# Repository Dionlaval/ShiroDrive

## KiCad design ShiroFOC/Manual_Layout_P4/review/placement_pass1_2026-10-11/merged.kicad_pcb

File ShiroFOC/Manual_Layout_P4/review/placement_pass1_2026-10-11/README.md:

# P4 — first IC and support placement pass

11 October 2026. This pass is saved in `../../ShiroFOC_Manual.kicad_pcb`, with routing presets in the matching `.kicad_pro`. The original P4 files are backed up in `before/`. P3 and the schematics were not edited.

## Result

All 18 ICs are within the 45 × 45 mm board outline. Forty existing footprints have changed position or orientation, and the schematic's fitted R618 has been added. The MCU and centred, locked encoder retain their original positions. The outline, mounting holes, power wire pads and six-layer stack are preserved.

There are now 212 footprint origins on the board, up from 179. Sixty-six remain staged: 50 fitted/default parts, 15 DNP parts and the SWD programming footprint. Fifty of these staged footprints belong to the DC-link capacitor bank (44 fitted, six DNP); the remaining input capacitors, bleeder and interfaces still need space. This pass therefore completes the IC placement, not the entire component placement.

[Front/back placement preview](preview/final/overview.png) shows actual footprint geometry and references. Both views use top-view coordinates; the back view is not mirrored. Copper fills are omitted for clarity. J1/J101 are intentionally shown as wire pads without the unused connector plastics.

## Placement decisions

- Preserve the repeated three-phase arrangement at the right, MCU below centre, auxiliary supplies above, and interfaces along the left and lower edges.
- Place U701 and its decoupling/I²C support between the MCU and auxiliary section, with access to the MCU's upper pins. Clear the centred encoder by moving the interfering resistors.
- Keep U602/U603 at the lower side, improve U602's position and nearby support, and bring C603/C605 close to their ICs. Add R618, 49.9 kΩ, between U604 ILIM and GND, matching its existing schematic symbol and path.
- Put C3/C7/C11 on the back alongside their phase stages, with VM pads facing the bridge's plated VM connections. Place TH701/TH702/TH703 beside their respective stages. Place C101/C102/C103/C110 as the first local DC-link ceramic bank.
- Bring reset, brake-input and temperature-divider support onto the board near the MCU/quiet analogue area. Leave the reset switch with the remaining interface placement rather than force it into the phase region.
- Rotate C203 to correct the existing bootstrap pad-to-track mismatch. Rotate R503 to shorten the brake-driver output/gate connection and add short local auxiliary/driver connections.

These are placement choices intended to support short loops and accessible routing. Final loop areas and return paths still depend on completing the copper.

## Routing setup and copper changes

Standard selectable trace widths are 0.1524 mm and 0.254 mm (6 and 10 mil). Default/analogue classes use 6 mil; gate and logic-power classes use 10 mil. Standalone through vias use 0.5 mm pads with 0.3 mm drills. Embedded plated thermal pads in the power footprints retain their native geometry.

The existing power-width and USB differential-pair settings are retained; their final sizing needs the power routing and final impedance stack. Existing preliminary traces were not globally resized.

Eighteen obsolete or obstructing copper guide objects were removed, and 32 short local track/via objects were added. Remaining half-bridge traces continue to indicate routing intent. See the individual manifests and `integration_repairs.json` for the exact changes.

## Verification

Native KiCad 9 DRC used the project rules and freshly filled zones. The comparison baseline was also refilled with the project settings.

The structural check passed: all existing electrical pad identities and schematic paths are preserved, R618 matches the schematic, and the MCU/encoder, board outline, four mounting holes and rule-area keepouts are unchanged. Four unused unnumbered mechanical locating pads belonging to J1/J101 were removed for the wire-only arrangement; their electrical pads are unchanged. All 18 IC envelopes fit; U1/U2/U3 have no courtyard polygons, so their native body/pad bounds were checked instead. Details are in `validation/final_structural_validation.json`.

| Native result | Before | After |
| --- | ---: | ---: |
| Errors | 64 | 33 |
| Warnings | 331 | 401 |
| Unconnected items | 456 | 444 |

No new error pairs were introduced, comparing violation type and item UUIDs. The remaining errors are 22 clearances, nine copper-to-edge clearances, and the two intentional connector-plastic courtyard overlaps at J1/J101. The latter are not physical conflicts for the planned soldered wires. New warnings are unfinished silkscreen and dangling ends left by guide removal; they have not been suppressed. See `final/drc.json` and `drc_comparison.json`.

Confidence: geometry, identities, dimensions and DRC results are verified from the native files. Routing quality remains a provisional placement assessment; this is not a completed routing or manufacturing release.

## Next layout pass

1. Finish the remaining DC-link bank/protection and service-interface placement, including reset/SWD and external temperature connections. Resolve the space required by the staged bulk capacitors before locking the power region. Optional DNP snubbers remain staged.
2. Route each phase's switching and gate/source-return loops, then the Kelvin shunt pairs; replace the preliminary copper as needed. Keep temperature and other quiet analogue traces clear of the switching nodes.
3. Finish MCU, sensor, feedback-selection and interface connections, with local decoupling returns and ground stitching.
4. Resolve the remaining real clearance/edge findings, finish silkscreen, refill zones, and run full connectivity/DRC checks again.

The primary board and project files are the working deliverables. Candidate files under `aux/`, `digital/`, `power/`, `control/` and `final/` are review history, not alternative project versions to edit.

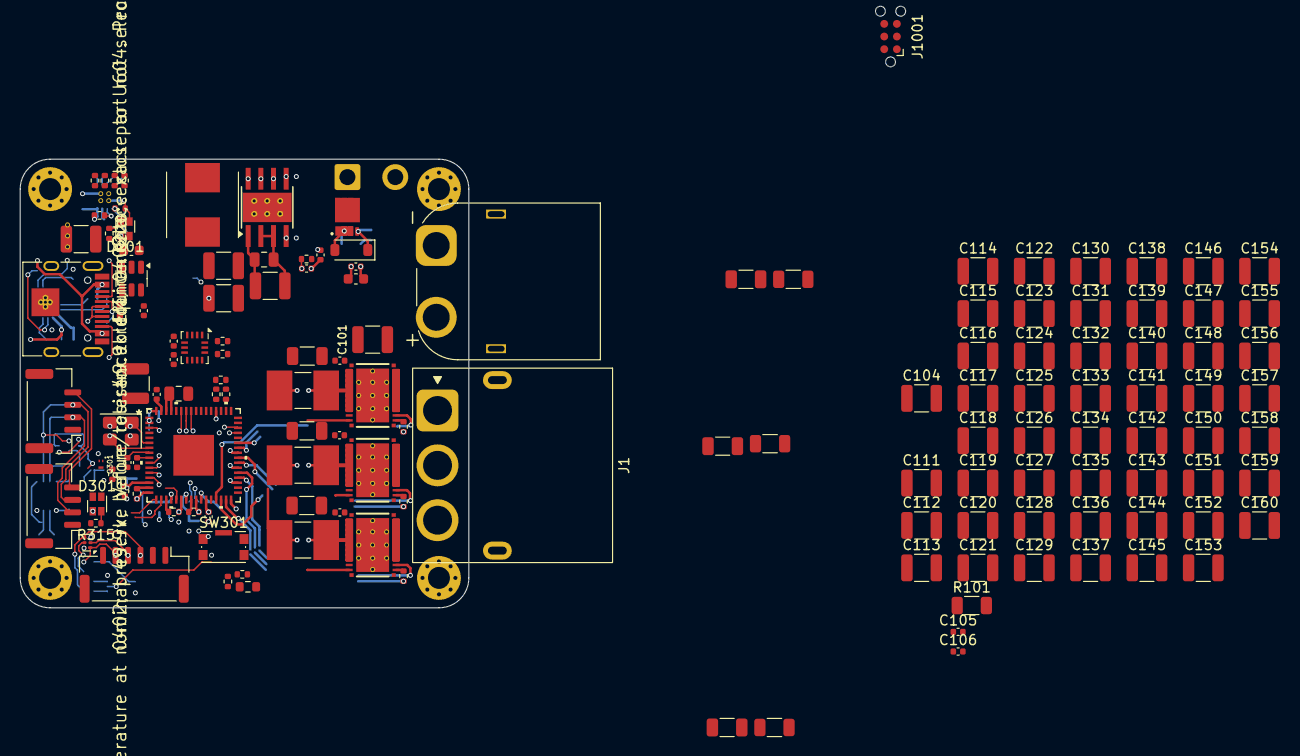
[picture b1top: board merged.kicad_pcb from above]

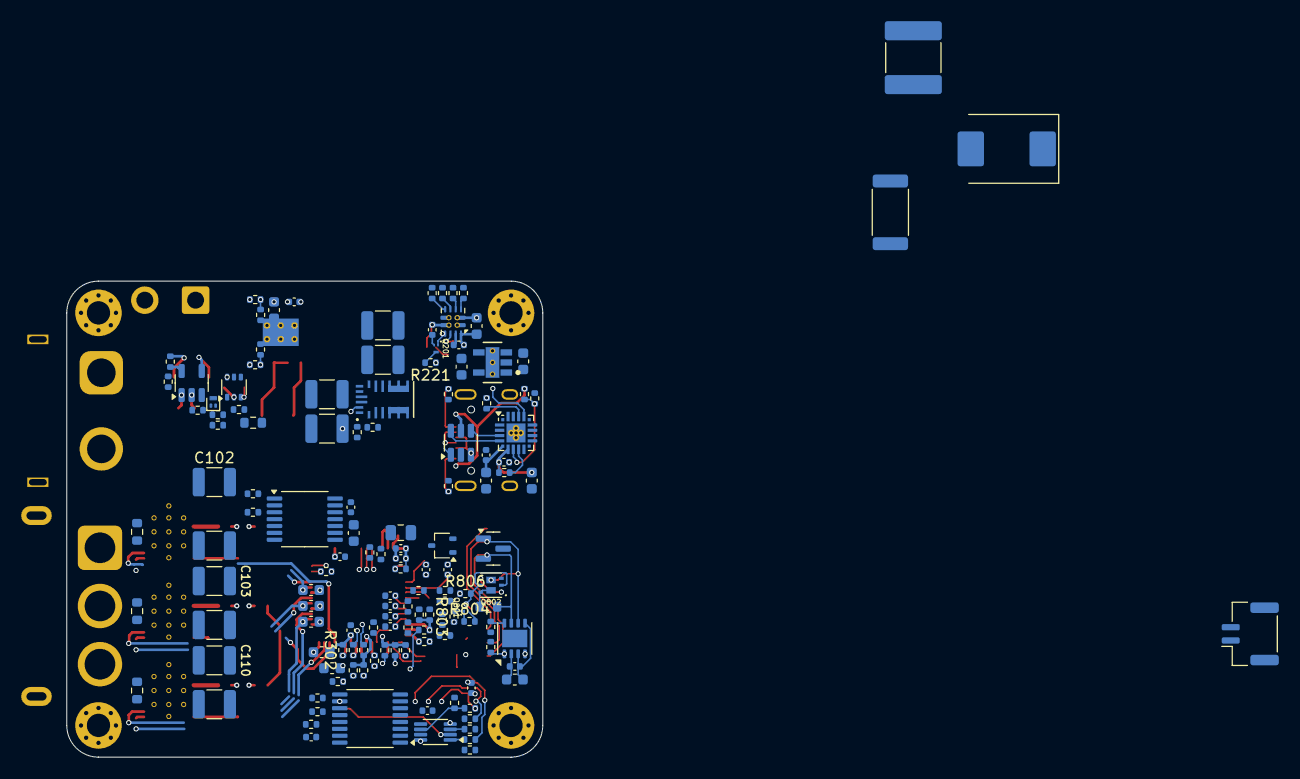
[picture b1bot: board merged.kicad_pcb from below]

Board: 6 copper layers, 45.0 x 45.0 mm, 278 parts (135 on the bottom side), 149 nets.

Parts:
C1, C5, C9, C108, C314, C711, C712, C713: 10nF; C_0402_1005Metric
C2, C6, C10: 1uF; C_1206_3216Metric
C3, C7, C11: 4.7uF; C_1210_3225Metric
C4, C8, C12: 220nF; C_0603_1608Metric
C101, C102, C103, C110, C111, C112, C113, C114, C115, C116, C117, C118, C119, C120, C121, C122, C123, C124, C127, C128, C129, C130, C131, C132, C133, C134, C135, C136, C137, C138, C139, C140, C141, C144, C145, C146, C147, C148, C149, C150, C151, C152, C153, C154, C155, C156, C157, C158: 10uF; C_1210_3225Metric
C104: 4.7uF 100V X7R; C_1210_3225Metric
C105: 100nF 100V X7R; C_0402_1005Metric
C106: 10nF 100V C0G; C_0402_1005Metric
C107: RC DAMP C - TUNE; C_2220_5750Metric
C125, C126, C142, C143, C159, C160: 10uF DNP; C_1210_3225Metric
C201: 2.2uF 100V X7R; C_1210_3225Metric
C202: 220nF 100V X7R; C_0805_2012Metric
C203, C209, C211, C301, C303, C305, C307, C310, C601, C603, C605, C701, C702, C801, C902, C904: 100nF; C_0402_1005Metric
C204, C304, C306, C602, C802: 1uF; C_0603_1608Metric
C205, C206, C214, C215: 22uF 25V X7R; C_1210_3225Metric
C208: 1uF 10V; C_0603_1608Metric
C210: 22uF 10V X7R; C_1210_3225Metric
C212, C213: 2.2uF 10V X7R; C_0603_1608Metric
C218, C219: 22uF 16V X7R; C_1210_3225Metric
C302: 10uF 10V; C_0805_2012Metric
C308, C309: 10pF C0G; C_0402_1005Metric
C311: 220nF 100V; C_0805_2012Metric
C312: 10uF 25V X7R; C_1210_3225Metric
C313: 100nF 25V; C_0402_1005Metric
C413, C423, C433: TUNE DNP; C_1206_3216Metric
C501: 1uF 25V; C_0603_1608Metric
C502, C503, C604: 100nF 50V; C_0402_1005Metric
C504: 1nF C0G; C_0402_1005Metric
C505: 100nF 16V; C_0402_1005Metric
C606: 4.7uF 16V X7R; C_0603_1608Metric
C607: 100nF 16V X7R; C_0402_1005Metric
C901, C903: 4.7uF 10V; C_0603_1608Metric
D101: VM TVS - SELECT AFTER TEST; D_SMC
D201, D301: LTST-C19HE1WT; LED_LiteOn_LTST-C19HE1WT
D501: BZT52C12 12V; D_SOD-123
D502: BAT54CM; SOT-883
D505: BAT54SW; SOT-323_SC-70
D601: TPD3E001DRYR; TPD3E001_DRY6
D801: PESD2CANFD24V-T; SOT-23
H1, H2, H3, H4: M2 PTH; MountingHole_2.2mm_M2_Pad_Via
J1: MR60PW-M; AMASS_MR60PW-M_1x03_P5.50mm_Horizontal
J101: AMASS XT60PW-M; AMASS_XT60PW-M_1x02_P7.20mm_Horizontal
J201: USB-C service; USB_C_Receptacle_HRO_TYPE-C-31-M-12
J501: BRAKE RESISTOR; SolderWire-0.75sqmm_1x02_P4.8mm_D1.25mm_OD2.3mm
J502: BRAKE NTC; JST_GH_SM02B-GHS-TB_1x02-1MP_P1.25mm_Horizontal
J601: EXT ENCODER / HALL; JST_GH_BM06B-GHS-TBT_1x06-1MP_P1.25mm_Vertical
J801: CAN 1; JST_GH_BM04B-GHS-TBT_1x04-1MP_P1.25mm_Vertical
J802: CAN 2; JST_GH_BM04B-GHS-TBT_1x04-1MP_P1.25mm_Vertical
J1001: TC2030-NL SWD; Tag-Connect_TC2030-IDC-NL_2x03_P1.27mm_Vertical
L201: 47uH / 1.9A; WE_LHMI_7050_74437349470
Q201, Q301, Q801: CSD17483F4; CSD17483F4_YJC0003A
Q501: ISZ080N10NM6 100V; ISZ080N10NM6_TSDSON8_FL
Q802: CSD87502Q2; CSD87502Q2_DLV0006A
R1, R3, R5: 0.5m 1%; R_Shunt_LR2512D_0m5_3W_Kelvin
R2, R4, R6: 4R7; R_0402_1005Metric
R101: 470k 0.25W; R_1206_3216Metric
R102: RC DAMP R - TUNE; R_2512_6332Metric
R103: 560k 0.1% 75V; R_0603_1608Metric
R105, R419, R429, R439: 28k 0.1%; R_0402_1005Metric
R106, R312, R711, R712, R713, R901: 1k; R_0402_1005Metric
R201: 100k 1%; R_0402_1005Metric
R202: 11.1k 1%; R_0402_1005Metric
R203, R204: 5.1k; R_0402_1005Metric
R206: 15.0k 1%; R_0402_1005Metric
R207, R209, R211, R213: 5.10k 1%; R_0402_1005Metric
R208: 10.0k 1%; R_0402_1005Metric
R210, R212: 22.0k 1%; R_0402_1005Metric
R214: 80.6k 1%; R_0402_1005Metric
R215, R220, R305, R306, R307, R309, R311, R315, R501, R504, R505, R604, R801, R805, R806: 10k; R_0402_1005Metric
R216: 34.0k 0.1%; R_0402_1005Metric
R217: 6.49k 0.1%; R_0402_1005Metric
R218, R219, R310, R615, R616, R617, R804: 100k; R_0402_1005Metric
R221: 33k; R_0402_1005Metric
R301, R302: 0R; R_0402_1005Metric
R303: 2k2; R_0402_1005Metric
R304: 15k; R_0402_1005Metric
R308, R715: 2.2k; R_0402_1005Metric
R313, R314: 22R; R_0402_1005Metric
R410, R420, R430, R441, R442, R443: 56k 0.1%; R_0402_1005Metric
R415, R425, R435: TUNE DNP; R_1206_3216Metric
R417, R418, R427, R428, R437, R438: 1k 0.1%; R_0402_1005Metric
R502, R611: 33R; R_0402_1005Metric
R503: 4.7R; R_0402_1005Metric
R506: 470k 1% 75V; R_0603_1608Metric
R509: 13.3k 1%; R_0402_1005Metric
R510: 1M 1%; R_0402_1005Metric
R511: 10k 1%; R_0402_1005Metric
R512, R701, R702, R703: 4.7k 1%; R_0402_1005Metric
R605, R606, R607, R902, R903: 100R; R_0402_1005Metric
R618: 49.9k 1%; R_0402_1005Metric
R802: 120R 1%; R_0603_1608Metric
R803: 4.7k; R_0402_1005Metric
R904: 22.1k 1%; R_0402_1005Metric
R905: 47.5k 1%; R_0402_1005Metric
SW301: RESET; SW_Push_1P1T-SH_NO_CK_KMR2xxG
TH701, TH702, TH703: 10k NTC B3380; R_0603_1608Metric
U1, U2, U3: CSD88599Q5DC; DMM0022A
U4: STSPIN32G4; QFN_IN32G4_STM
U201: LMR36510FADDAR; LMR36510_DDA
U202: USBLC6-2SC6; USBLC6_SOT23_6
U203: TPS2121RUXR; TPS2121_RUX
U204: TLV75533PDYDR; TLV75533_DYD_GND
U205: MPM3620AGQV-Z; IC18_MPM3620AGQV-Z_MNP
U501: UCC27517ADBVR; UCC27517A_DBV5
U502: TLV3012BIDCKR; SOT-363_SC-70-6
U601: AS5047P-ATSM; AS5047P_TSSOP14
U602: TMUX1574PW; TMUX1574_PW16
U603: 74LVC3G17; VSSOP-8_2.3x2mm_P0.5mm
U604: TPS2553DBVR; SOT-23-6
U701: BMI323; BMI323_LGA14
U801: TCAN3413DRBR; TCAN3413_DRB8
U901: CP2102N-A02-GQFN20; SiliconLabs_QFN-20-1EP_3x3mm_P0.5mm_EP1.8x1.8mm_ThermalVias
Y301: 24MHz 7pF; Crystal_SMD_3225-4Pin_3.2x2.5mm

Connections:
3V3: C213.1, C301.1, C302.1, C307.1, C503.1, C601.1, C602.1, C603.1, C605.1, C701.1, C702.1, C801.1, C802.1, C901.1, C902.1, C903.1, C904.1, D505.2 (K), J1001.1 (VCC), R301.1, R303.1, R305.1, R308.1, R309.1, R310.1, R511.1, R604.1, R701.1, R702.1, R703.1, R715.1, R801.1, R805.1, R901.1, U4.1 (REG3V3/VDD), U4.2 (VBAT), U4.64 (REGIN), U204.5 (OUT), U502.6 (VDD), U601.11 (VDD), U601.12 (VDD3V3), U602.16 (VDD), U603.8 (VCC), U701.5 (VDDIO), U701.8 (VDD), U701.12 (CSB), U801.3 (VCC), U801.5 (VIO), U901.6 (VDD), U901.7 (VREGIN)
5V_BAT: C218.1, C219.1, R206.1, R210.1, R216.1, U203.7 (IN1), U205.7 (OUT), U205.8 (OUT), U205.9 (OUT)
5V_SYS: C210.1, C211.1, C212.1, C606.1, D201.4 (A), D301.4 (A), R215.1, U203.1 (OUT), U203.8 (OUT), U204.1 (IN), U204.3 (EN), U604.1 (IN), U604.3 (EN)
5V_USB: C208.1, J201.A4 (VBUS), J201.A9 (VBUS), J201.B4 (VBUS), J201.B9 (VBUS), R208.1, R212.1, R904.1, U202.5 (VBUS), U203.2 (IN2)
/5 V / 3.3 V power/10V_FB: R201.2, R202.1, U201.5 (FB)
/5 V / 3.3 V power/10V_GOOD: R218.2, R219.1, U201.4 (PG), U205.17 (EN)
/5 V / 3.3 V power/U205_AGND: R217.2, U205.3 (AGND)
/5 V / 3.3 V power/U205_SW: U205.4 (SW), U205.5 (SW), U205.6 (SW)
/Brake chopper/BRAKE_NTC_RAW: J502.1, R511.2, R512.1
/Brake chopper/BRAKE_OV_CMD: D502.2 (A2), R510.1, U502.1 (OUT)
/Brake chopper/BRAKE_PWM_DRV: D502.3 (CC), R505.1, U501.3 (IN+)
/CAN interface/CANH_BUS: D801.2 (CANH_IN), J801.2, J802.2, R802.1, U801.7 (CANH)
/CAN interface/CANL_BUS: D801.1 (CANL_IN), J801.3, J802.3, Q802.3 (D2), U801.6 (CANL)
/CAN interface/CAN_SHIELD: J801.4, J802.4
/Current / temperature/NTC_A_RAW: R701.2, R711.1, TH701.1
/Current / temperature/NTC_B_RAW: R702.2, R712.1, TH702.1
/Current / temperature/NTC_C_RAW: R703.2, R713.1, TH703.1
/Current / temperature/OPN_U1: R418.2, R419.2, U4.16 (-)
/Current / temperature/OPN_V1: R428.2, R429.2, U4.22 (-)
/Current / temperature/OPN_W1: R438.2, R439.2, U4.25 (-)
/Current / temperature/OPP_U1: R410.2, R417.2, R441.1, U4.14 (+)
/Current / temperature/OPP_V1: R420.2, R427.2, R442.1, U4.20 (+)
/Current / temperature/OPP_W1: R430.2, R437.2, R443.1, U4.23 (+)
/External feedback/EXT_VCC: C607.1, J601.1, U604.6 (OUT)
/External feedback/FB_ESD_RAIL: C604.1, D601.6 (VCC)
/MCU / clock / SWD/NRST: C310.1, J1001.3 (~RESET), R303.2, SW301.1, U4.8 (PG10/NRST)
/MCU / clock / SWD/SWCLK: J1001.4 (SWCLK), U4.50 (PA14/SWCLK)
/MCU / clock / SWD/SWDIO: J1001.2 (SWDIO), U4.49 (PA13/SWDIO)
/Three-phase bridge/LS_SOURCE_U: C413.2, R3.1 (POWER+), U1.12 (PGND), U1.13 (PGND), U1.14 (PGND), U1.15 (PGND), U1.16 (PGND), U1.17 (PGND), U1.18 (PGND), U1.19 (PGND), U1.20 (PGND)
/Three-phase bridge/LS_SOURCE_V: C423.2, R1.1 (POWER+), U2.12 (PGND), U2.13 (PGND), U2.14 (PGND), U2.15 (PGND), U2.16 (PGND), U2.17 (PGND), U2.18 (PGND), U2.19 (PGND), U2.20 (PGND)
/Three-phase bridge/LS_SOURCE_W: C433.2, R5.1 (POWER+), U3.12 (PGND), U3.13 (PGND), U3.14 (PGND), U3.15 (PGND), U3.16 (PGND), U3.17 (PGND), U3.18 (PGND), U3.19 (PGND), U3.20 (PGND)
/USB service/CP2102_RST_N: R901.2, U901.9 (RST)
/USB service/CP2102_VBUS_SENSE: R904.2, R905.1, U901.8 (VBUS)
/USB service/UART_BRIDGE_RX: R903.2, U901.17 (RXD)
/USB service/UART_BRIDGE_TX: R902.1, U901.18 (TXD)
/USB service/USB_CC1: J201.A5 (CC1), R203.1
/USB service/USB_CC2: J201.B5 (CC2), R204.1
/USB service/USB_DM: U202.6 (IO1), U901.5 (D-)
/USB service/USB_DM_CONN: J201.A7 (D-), J201.B7 (D-), U202.1 (IO1)
/USB service/USB_DP: U202.4 (IO2), U901.4 (D+)
/USB service/USB_DP_CONN: J201.A6 (D+), J201.B6 (D+), U202.3 (IO2)
AS5047P_CS_N: R309.2, U4.51 (PA15), U601.1 (CSn)
BOOTSTRAP1: C4.2, U4.41 (BOOTSTRAP1)
BOOTSTRAP2: C8.2, U4.38 (BOOTSTRAP2)
BOOTSTRAP3: C12.2, U4.35 (BOOTSTRAP3)
BRAKE_PWM: R501.1, R502.1, U4.60 (PB9)
CAN_STB: R801.2, U4.28 (PB10), U801.8 (STB)
CAN_TERM_DISABLE: R803.1, U4.5 (PC15)
CAN_TERM_GATE: Q301.1 (G), Q801.3 (D), Q802.2 (G1), Q802.5 (G2), R806.2
EXT_FEEDBACK_SELECT: R306.1, U4.53 (PD2), U602.1 (SEL)
EXT_SENSOR_FAULT_N: R604.2, U4.3 (PC13), U604.4 (~FAULT)
FDCAN1_RX: U4.47 (PA11), U801.4 (RXD)
FDCAN1_TX: R805.2, U4.48 (PA12), U801.1 (TXD)
FEEDBACK_A_H1: U4.57 (PB6), U602.4 (D1)
FEEDBACK_B_H2: U4.58 (PB7), U602.7 (D2)
FEEDBACK_I_H3: R307.1, U4.59 (PB8/BOOT0), U602.9 (D3)
GHS1: R2.2, U4.43 (GHS1)
GHS2: R4.2, U4.40 (GHS2)
GHS3: R6.2, U4.37 (GHS3)
GLS1: U1.22 (GL), U4.29 (GLS1)
GLS2: U2.22 (GL), U4.30 (GLS2)
GLS3: U3.22 (GL), U4.31 (GLS3)
GND: C1.2, C2.2, C3.2, C5.2, C6.2, C7.2, C9.2, C10.2, C11.2, C101.2, C102.2, C103.2, C104.2, C105.2, C106.2, C107.2, C108.2, C110.2, C111.2, C112.2, C113.2, C114.2, C115.2, C116.2, C117.2, C118.2, C119.2, C120.2, C121.2, C122.2, C123.2, C124.2, C125.2, C126.2, C127.2, C128.2, C129.2, C130.2, C131.2, C132.2, C133.2, C134.2, C135.2, C136.2, C137.2, C138.2, C139.2, C140.2, C141.2, C142.2, C143.2, C144.2, C145.2, C146.2, C147.2, C148.2, C149.2, C150.2, C151.2, C152.2, C153.2, C154.2, C155.2, C156.2, C157.2, C158.2, C159.2, C160.2, C201.2, C202.2, C204.2, C205.2, C206.2, C208.2, C209.2, C210.2, C211.2, C212.2, C213.2, C214.2, C215.2, C218.2, C219.2, C301.2, C302.2, C303.2, C304.2, C305.2, C306.2, C307.2, C308.2, C309.2, C310.2, C311.2, C312.2, C313.2, C314.2, C501.2, C502.2, C503.2, C504.2, C505.2, C601.2, C602.2, C603.2, C604.2, C605.2, C606.2, C607.2, C701.2, C702.2, C711.2, C712.2, C713.2, C801.2, C802.2, C901.2, C902.2, C903.2, C904.2, D101.2 (A), D501.2 (A), D505.1 (A), D601.3 (GND), D801.3 (GND), J101.1, J201.A1 (GND), J201.A12 (GND), J201.B1 (GND), J201.B12 (GND), J201.S1 (SHIELD), J502.2, J502.MP (MOUNT), J601.2, J601.6, J601.MP (MOUNT), J801.1, J801.MP (MOUNT), J802.1, J802.MP (MOUNT), J1001.5 (GND), Q201.2 (S), Q301.2 (S), Q501.1 (S), Q501.2 (S), Q501.3 (S), Q801.2 (S), R1.4 (POWER-), R3.4 (POWER-), R5.4 (POWER-), R101.2, R105.2, R202.2, R203.2, R204.2, R207.2, R209.2, R211.2, R213.2, R214.2, R219.2, R220.2, R306.2, R307.2, R311.2, R315.2, R441.2, R442.2, R443.2, R501.2, R504.2, R505.2, R509.2, R615.2, R616.2, R617.2, R618.2, R804.2, R905.2, SW301.2, SW301.SH (B), TH701.2, TH702.2, TH703.2, U4.32 (PGND), U4.65 (VSS/EP), U201.1 (PGND), U201.9 (GND), U202.2 (GND), U203.12 (GND), U204.2 (GND), U205.12 (PGND), U205.13 (PGND), U205.14 (PGND), U501.2 (GND), U501.4 (IN-), U502.2 (GND), U601.5 (TEST), U601.13 (GND), U602.2 (S1A), U602.5 (S2A), U602.8 (GND), U602.11 (S3A), U603.4 (GND), U604.2 (GND), U701.1 (SDO/SA0), U701.6 (GNDIO), U701.7 (GND), U801.2 (GND), U801.9 (EP), U901.3 (GND), U901.12 (GND), U901.21 (EP), Y301.2, Y301.4
HS_RETURN_U: C4.1, U1.2 (SH), U4.42 (OUT1)
HS_RETURN_V: C8.1, U2.2 (SH), U4.39 (OUT2)
HS_RETURN_W: C12.1, U3.2 (SH), U4.36 (OUT3)
I2C2_SCL: R308.2, U4.21 (PC4), U701.13 (SCK/SCL)
I2C2_SDA: R715.2, U4.44 (PA8), U701.14 (SDI/SDA)
IMU_INT1: U4.17 (PA4), U701.4 (INT1)
IMU_INT2: U4.18 (PA5), U701.9 (INT2)
INPUT_MUX_ENABLE_N: R305.2, U4.4 (PC14), U602.15 (EN_N)
NTC_BRAKE: C505.1, D505.3 (COM), R512.2, U4.10 (PC1)
NTC_PHASE_A: C711.1, R711.2, U4.12 (PC3)
NTC_PHASE_B: C712.1, R712.2, U4.11 (PC2)
NTC_PHASE_C: C713.1, R713.2, U4.13 (PA0)
unnamed: C107.1, R102.2
unnamed: C413.1, R415.2
unnamed: C423.1, R425.2
unnamed: C433.1, R435.2
unnamed: D201.3 (BK), R220.1
unnamed: D201.2 (GK), R221.1
unnamed: D301.3 (BK), R315.1
unnamed: D301.1 (RK), R304.2
unnamed: D501.1 (K), Q501.4 (G), R503.2, R504.1
unnamed: D502.1 (A1), R502.2
unnamed: D601.1 (IO1), J601.5, R607.1
unnamed: D601.2 (IO2), D601.5 (NC), J601.4, R606.1
unnamed: D601.4 (IO3), J601.3, R605.1
unnamed: J501.1, Q501.5 (D), Q501.6 (D), Q501.7 (D), Q501.8 (D)
unnamed: Q201.3 (D), R221.2
unnamed: Q301.3 (D), R304.1
unnamed: Q801.1 (G), R803.2, R804.1
unnamed: Q802.6 (D1), R802.2
unnamed: Q802.1 (S1), Q802.4 (S2)
unnamed: R103.2, R105.1, R106.1
unnamed: R310.2, R311.1, R312.1
unnamed: R605.2, R615.1, U603.1
unnamed: R606.2, R616.1, U603.3
unnamed: R607.2, R617.1, U603.6
unnamed: R2.1, U1.1 (GH)
unnamed: R4.1, U2.1 (GH)
unnamed: R6.1, U3.1 (GH)
unnamed: C308.1, U4.6 (PF0), Y301.1
unnamed: C309.1, U4.7 (PF1), Y301.3
unnamed: C314.1, R312.2, U4.52 (SCREF)
unnamed: C203.1, U201.7 (BOOT)
unnamed: C203.2, L201.1, U201.8 (SW)
unnamed: C204.1, U201.6 (VCC)
unnamed: R208.2, R209.1, U203.3 (CP2)
unnamed: R214.1, U203.10 (ILM)
unnamed: R210.2, R211.1, U203.5 (OV1)
unnamed: R212.2, R213.1, U203.4 (OV2)
unnamed: R206.2, R207.1, U203.6 (PR1)
unnamed: C209.1, U203.11 (SS)
unnamed: R216.2, R217.1, U205.1 (FB)
unnamed: R503.1, U501.5 (OUT)
unnamed: C504.1, R506.2, R509.1, R510.2, U502.3 (IN+)
unnamed: U502.4 (IN-), U502.5 (REF)
unnamed: R313.2, U601.2 (CLK)
unnamed: R611.1, U601.3 (MISO)
unnamed: R314.2, U601.4 (MOSI)
unnamed: U602.3 (S1B), U603.7
unnamed: U602.6 (S2B), U603.5
unnamed: U602.10 (S3B), U603.2
unnamed: R618.1, U604.5 (ILIM)
OPO_U1: R419.1, U4.15 (OUT)
OPO_V1: R429.1, U4.19 (OUT)
OPO_W1: R439.1, U4.24 (OUT)
PHASE_U: J1.1 (U), R415.1, U1.3 (VSW), U1.4 (VSW), U1.5 (VSW), U1.6 (VSW), U1.7 (VSW), U1.8 (VSW), U1.9 (VSW), U1.10 (VSW), U1.11 (VSW)
PHASE_V: J1.2 (V), R425.1, U2.3 (VSW), U2.4 (VSW), U2.5 (VSW), U2.6 (VSW), U2.7 (VSW), U2.8 (VSW), U2.9 (VSW), U2.10 (VSW), U2.11 (VSW)
PHASE_W: J1.3 (W), R435.1, U3.3 (VSW), U3.4 (VSW), U3.5 (VSW), U3.6 (VSW), U3.7 (VSW), U3.8 (VSW), U3.9 (VSW), U3.10 (VSW), U3.11 (VSW)
PWR_SOURCE_STATUS: Q201.1 (G), R215.2, U203.9 (ST)
SHUNT_U_SENSE_N: R3.3 (SENSE-), R418.1
SHUNT_U_SENSE_P: R3.2 (SENSE+), R417.1
SHUNT_V_SENSE_N: R1.3 (SENSE-), R428.1
SHUNT_V_SENSE_P: R1.2 (SENSE+), R427.1
SHUNT_W_SENSE_N: R5.3 (SENSE-), R438.1
SHUNT_W_SENSE_P: R5.2 (SENSE+), R437.1
SPI3_MISO: R611.2, U4.55 (PB4)
SPI3_MOSI_MCU: R314.1, U4.56 (PB5)
SPI3_SCK_MCU: R313.1, U4.54 (PB3)
USB_UART_RX: R902.2, U4.46 (PA10)
USB_UART_TX: R903.1, U4.45 (PA9)
VBUS_MUX_IN: R106.2, U602.13 (S4A), U602.14 (S4B)
VBUS_SENSE: C108.1, U4.9 (PC0), U602.12 (D4)
VCC: C205.1, C206.1, C214.1, C215.1, C312.1, C313.1, C501.1, C502.1, L201.2, R201.1, R218.1, R806.1, U4.63 (VCC), U205.16 (IN), U501.1 (VDD)
VDDA: C303.1, C304.1, R301.2, R302.1, U4.27 (VDDA)
VM: C1.1, C2.1, C3.1, C5.1, C6.1, C7.1, C9.1, C10.1, C11.1, C101.1, C102.1, C103.1, C104.1, C105.1, C106.1, C110.1, C111.1, C112.1, C113.1, C114.1, C115.1, C116.1, C117.1, C118.1, C119.1, C120.1, C121.1, C122.1, C123.1, C124.1, C125.1, C126.1, C127.1, C128.1, C129.1, C130.1, C131.1, C132.1, C133.1, C134.1, C135.1, C136.1, C137.1, C138.1, C139.1, C140.1, C141.1, C142.1, C143.1, C144.1, C145.1, C146.1, C147.1, C148.1, C149.1, C150.1, C151.1, C152.1, C153.1, C154.1, C155.1, C156.1, C157.1, C158.1, C159.1, C160.1, C201.1, C202.1, C311.1, D101.1 (K), J101.2, J501.2, R101.1, R102.1, R103.1, R506.1, U1.27 (VIN), U2.27 (VIN), U3.27 (VIN), U4.61 (VM), U4.62 (SW), U201.2 (VIN), U201.3 (EN)
VREF+: C305.1, C306.1, R302.2, R410.1, R420.1, R430.1, U4.26 (VREF+)

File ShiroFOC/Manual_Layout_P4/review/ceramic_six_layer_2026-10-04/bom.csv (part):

"References","Value","Footprint","Quantity","DNP","Manufacturer","MPN","LCSC"
"C1,C5,C9","10nF","Capacitor_SMD:C_0402_1005Metric","3","","TDK","C1005X7S2A103K050BB",""
"C2,C6,C10","1uF","Capacitor_SMD:C_1206_3216Metric","3","","TDK","C3216X7R2A105K160AA",""
"C3,C7,C11","4.7uF","Capacitor_SMD:C_1210_3225Metric","3","","TDK","C3225X7S2A475K200AB",""
"C4,C8,C12","220nF","Capacitor_SMD:C_0603_1608Metric","3","","TDK","C1608X7R1H224K080AB",""
"C101-C103,C110-C124,C127-C141,C144-C158","10uF","Capacitor_SMD:C_1210_3225Metric","48","","Samsung Electro-Mechanics","CL32Y106KCVZNWE","C3840810"
"C104","4.7uF 100V X7R","Capacitor_SMD:C_1210_3225Metric","1","","","",""
"C105","100nF 100V X7R","Capacitor_SMD:C_0402_1005Metric","1","","","",""
"C106","10nF 100V C0G","Capacitor_SMD:C_0402_1005Metric","1","","","",""
"C107","RC DAMP C - TUNE","Capacitor_SMD:C_2220_5750Metric","1","DNP","","",""
"C108,C314,C711-C713","10nF","Capacitor_SMD:C_0402_1005Metric","5","","","",""
"C125,C126,C142,C143,C159,C160","10uF DNP","Capacitor_SMD:C_1210_3225Metric","6","DNP","Samsung Electro-Mechanics","CL32Y106KCVZNWE","C3840810"
"C201","2.2uF 100V X7R","Capacitor_SMD:C_1210_3225Metric","1","","","",""
"C202","220nF 100V X7R","Capacitor_SMD:C_0805_2012Metric","1","","","",""
"C203,C209,C211,C301,C303,C305,C307,C310,C601,C603,C605,C701,C702,C801,C902,C904","100nF","Capacitor_SMD:C_0402_1005Metric","16","","","",""
"C204,C304,C306,C602,C802","1uF","Capacitor_SMD:C_0603_1608Metric","5","","","",""
"C205,C206,C214,C215","22uF 25V X7R","Capacitor_SMD:C_1210_3225Metric","4","","TDK","C3225X7R1E226M250AB",""
"C207","4.7nF 2kV","Capacitor_SMD:C_1206_3216Metric","1","DNP","","",""
"C208","1uF 10V","Capacitor_SMD:C_0603_1608Metric","1","","","",""
"C210","22uF 10V X7R","Capacitor_SMD:C_1210_3225Metric","1","","","",""
"C212,C213","2.2uF 10V X7R","Capacitor_SMD:C_0603_1608Metric","2","","","",""
"C218,C219","22uF 16V X7R","Capacitor_SMD:C_1210_3225Metric","2","","TDK","C3225X7R1C226M250AC",""
"C302","10uF 10V","Capacitor_SMD:C_0805_2012Metric","1","","","",""
"C308,C309","10pF C0G","Capacitor_SMD:C_0402_1005Metric","2","","","",""
"C311","220nF 100V","Capacitor_SMD:C_0805_2012Metric","1","","","",""
"C312","10uF 25V X7R","Capacitor_SMD:C_1210_3225Metric","1","","","",""
"C313","100nF 25V","Capacitor_SMD:C_0402_1005Metric","1","","","",""
"C413,C423,C433","TUNE DNP","Capacitor_SMD:C_1206_3216Metric","3","DNP","","",""
"C414,C424,C434","47pF C0G","Capacitor_SMD:C_0603_1608Metric","3","DNP","TDK","C1608C0G1H470J080AA",""
"C501","1uF 25V","Capacitor_SMD:C_0603_1608Metric","1","","TDK","C1608X7R1E105K080AB",""
"C502,C503,C604","100nF 50V","Capacitor_SMD:C_0402_1005Metric","3","","TDK","",""
"C504","1nF C0G","Capacitor_SMD:C_0603_1608Metric","1","","TDK","C1608C0G1H102J080AA",""
"C505","100nF 16V","Capacitor_SMD:C_0402_1005Metric","1","","","",""
"C606","4.7uF 16V X7R","Capacitor_SMD:C_0603_1608Metric","1","","","",""
"C607","100nF 16V X7R","Capacitor_SMD:C_0402_1005Metric","1","","","",""
"C901,C903","4.7uF 10V","Capacitor_SMD:C_0603_1608Metric","2","","","",""
"D101","VM TVS - SELECT AFTER TEST","Diode_SMD:D_SMC","1","DNP","","",""
"D301","RED","LED_SMD:LED_0603_1608Metric","1","","","",""
"D501","BZT52C12 12V","Diode_SMD:D_SOD-123","1","","Diodes Incorporated","BZT52C12-7-F",""
"D502,D503","BAT54H","Diode_SMD:D_SOD-123F","2","","","BAT54H,115",""
"D505","BAT54S","Package_TO_SOT_SMD:SOT-23","1","","","BAT54S,215",""
"D601","TPD3E001DRLR 3-line ESD","Manual:TPD3E001_DRL5","1","","","TPD3E001DRLR",""
"D801","PESD2CANFD24V-T","Package_TO_SOT_SMD:SOT-23","1","","","PESD2CANFD24V-T",""
"J101","AMASS XT60PW-M","Connector_AMASS:AMASS_XT60PW-M_1x02_P7.20mm_Horizontal","1","","","XT60PW-M",""
"J201","USB-C service","Connector_USB:USB_C_Receptacle_HRO_TYPE-C-31-M-12","1","","","TYPE-C-31-M-12",""
"J501","BRAKE RESISTOR","Connector_Wire:SolderWire-2sqmm_1x02_P7.8mm_D2mm_OD3.9mm","1","","","PCB feature",""
"J502","BRAKE NTC","Connector_JST:JST_GH_SM02B-GHS-TB_1x02-1MP_P1.25mm_Horizontal","1","","","SM02B-GHS-TB(LF)(SN)",""
"J601","EXT ENCODER / HALL","Connector_JST:JST_GH_BM06B-GHS-TBT_1x06-1MP_P1.25mm_Vertical","1","","","BM06B-GHS-TBT",""
"J801","CAN 1","Connector_JST:JST_GH_BM04B-GHS-TBT_1x04-1MP_P1.25mm_Vertical","1","","","BM04B-GHS-TBT",""
"J802","CAN 2","Connector_JST:JST_GH_BM04B-GHS-TBT_1x04-1MP_P1.25mm_Vertical","1","","","BM04B-GHS-TBT",""
"JP801","TERM ENABLE","Jumper:SolderJumper-2_P1.3mm_Open_Pad1.0x1.5mm","1","DNP","","",""
"L201","47uH / 1.9A","Manual:WE_LHMI_7050_74437349470","1","","Wurth Elektronik","74437349470",""
"Q501","CSD19531Q5A 100V","Manual:CSD19531Q5A_Q5A_DQJ0008A","1","","","CSD19531Q5A",""
"R1,R3,R5","0.5m 1%","Manual:R_Shunt_LR2512D_0m5_3W_Kelvin","3","","Milliohm","LR2512D-3W-0.5mR-1%",""
"R2,R4,R6","4R7","Resistor_SMD:R_0402_1005Metric","3","","YAGEO","",""
"R101","470k 0.25W","Resistor_SMD:R_1206_3216Metric","1","","","",""
"R102","RC DAMP R - TUNE","Resistor_SMD:R_2512_6332Metric","1","DNP","","",""
"R103","560k 0.1% 75V","Resistor_SMD:R_0603_1608Metric","1","","Yageo","RT0603BRD07560KL","C719312"
"R105","28k 0.1%","Resistor_SMD:R_0402_1005Metric","1","","Yageo","RT0402BRD0728KL","C852686"
"R106,R312,R711-R713,R901","1k","Resistor_SMD:R_0402_1005Metric","6","","","",""
"R201","100k 1%","Resistor_SMD:R_0402_1005Metric","1","","","",""
"R202","11.1k 1%","Resistor_SMD:R_0402_1005Metric","1","","","",""
"R203,R204","5.1k","Resistor_SMD:R_0402_1005Metric","2","","","",""
"R205,R301,R302","0R","Resistor_SMD:R_0402_1005Metric","3","","","",""
"R206","15.0k 1%","Resistor_SMD:R_0402_1005Metric","1","","","",""
"R207,R209,R211,R213","5.10k 1%","Resistor_SMD:R_0402_1005Metric","4","","","",""
"R208","10.0k 1%","Resistor_SMD:R_0402_1005Metric","1","","","",""
"R210,R212","22.0k 1%","Resistor_SMD:R_0402_1005Metric","2","","Yageo","",""
"R214","80.6k 1%","Resistor_SMD:R_0402_1005Metric","1","","","",""
"R215,R305-R307,R309,R311,R501,R504,R505,R604,R801,R805","10k","Resistor_SMD:R_0402_1005Metric","12","","Yageo","",""
"R216","34.0k 0.1%","Resistor_SMD:R_0402_1005Metric","1","","","",""
"R217","6.49k 0.1%","Resistor_SMD:R_0402_1005Metric","1","","","",""
"R218,R219,R310,R615-R617","100k","Resistor_SMD:R_0402_1005Metric","6","","","",""
"R303","2k2","Resistor_SMD:R_0402_1005Metric","1","","","",""
"R304,R308,R715","2.2k","Resistor_SMD:R_0402_1005Metric","3","","","",""
"R313,R314","22R","Resistor_SMD:R_0402_1005Metric","2","","","",""
"R410,R420,R430,R441-R443","56k 0.1%","Resistor_SMD:R_0402_1005Metric","6","","YAGEO","",""
"R415,R425,R435","TUNE DNP","Resistor_SMD:R_1206_3216Metric","3","DNP","","",""
"R417,R418,R427,R428,R437,R438","1k 0.1%","Resistor_SMD:R_0402_1005Metric","6","","YAGEO","",""
"R419,R429,R439","28k 0.1%","Resistor_SMD:R_0402_1005Metric","3","","YAGEO","",""
"R502,R611","33R","Resistor_SMD:R_0402_1005Metric","2","","Yageo","",""
"R503","4.7R","Resistor_SMD:R_0402_1005Metric","1","","Yageo","",""
"R506","470k 1% 75V","Resistor_SMD:R_0603_1608Metric","1","","Yageo","RC0603FR-07470KL","C114622"
"R509","13.3k 1%","Resistor_SMD:R_0402_1005Metric","1","","Yageo","RC0402FR-0713K3L","C274352"
"R510","1M 1%","Resistor_SMD:R_0402_1005Metric","1","","Yageo","RC0402FR-071ML","C138033"
"R511","10k 1%","Resistor_SMD:R_0402_1005Metric","1","","","",""
"R512,R701-R703","4.7k 1%","Resistor_SMD:R_0402_1005Metric","4","","","",""
"R605-R607,R902,R903","100R","Resistor_SMD:R_0402_1005Metric","5","","","",""
"R608-R610","4.7k DNP","Resistor_SMD:R_0402_1005Metric","3","DNP","","",""
"R802","120R 1%","Resistor_SMD:R_0603_1608Metric","1","","","",""
"R803","0R CANH link","Resistor_SMD:R_0402_1005Metric","1","","","",""
"R804","0R CANL link","Resistor_SMD:R_0402_1005Metric","1","","","",""
"R904","22.1k 1%","Resistor_SMD:R_0402_1005Metric","1","","","",""
"R905","47.5k 1%","Resistor_SMD:R_0402_1005Metric","1","","","",""
"SW301","RESET","Button_Switch_SMD:SW_Push_1P1T-SH_NO_CK_KMR2xxG","1","","C&K / Littelfuse","KMR221GLFS",""
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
